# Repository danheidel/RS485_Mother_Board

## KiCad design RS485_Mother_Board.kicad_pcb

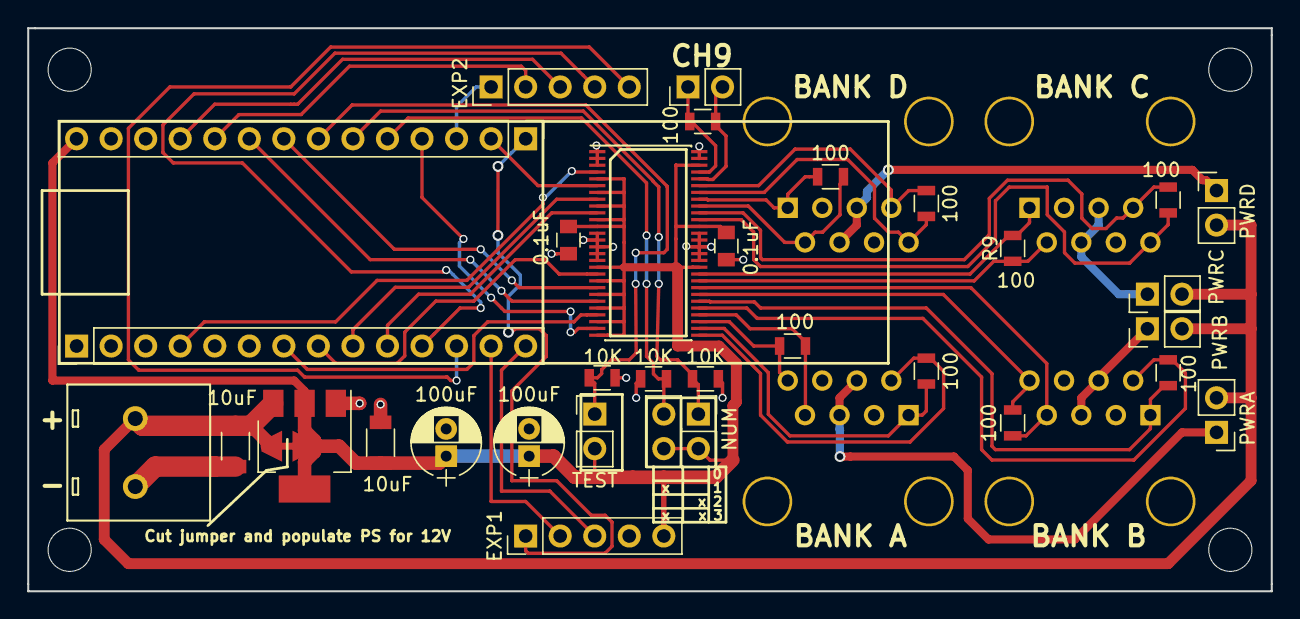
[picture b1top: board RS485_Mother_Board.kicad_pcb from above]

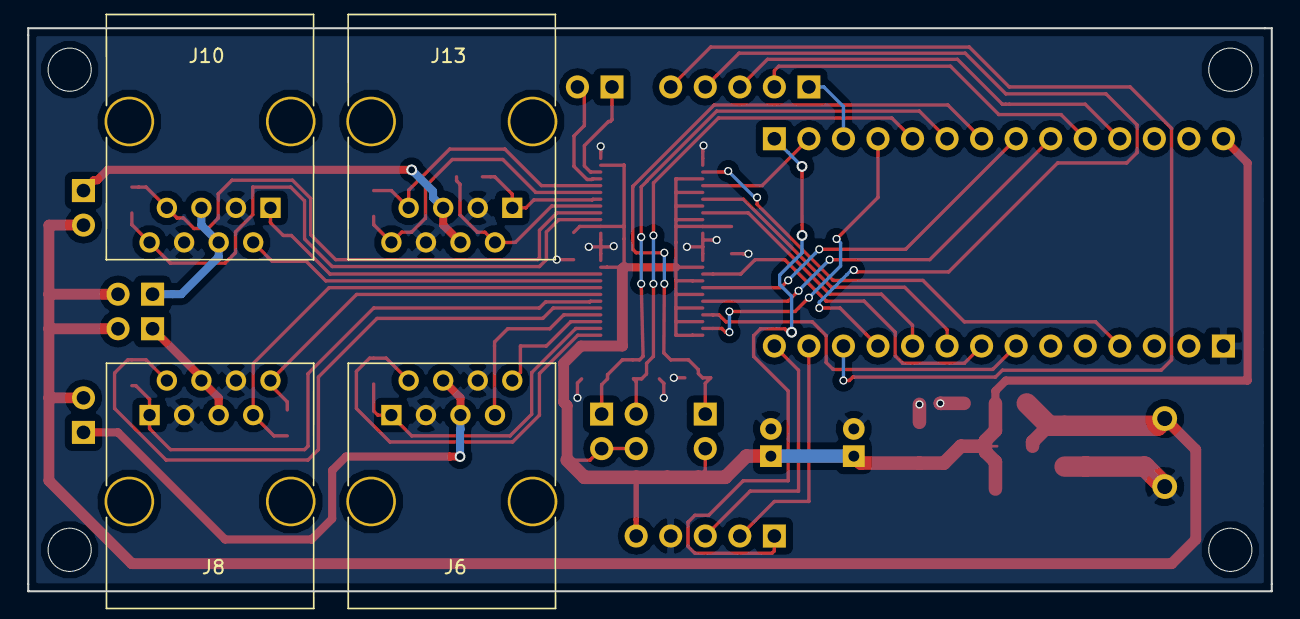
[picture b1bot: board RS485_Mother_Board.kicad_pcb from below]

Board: 2 copper layers, 91.4 x 41.4 mm, 37 parts (4 on the bottom side), 45 nets.

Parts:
C1, C2: 10uF; C_1206
C3, C4: 100uF; CP_Radial_D5.0mm_P2.00mm
C5, C6: 0.1uF; C_0805
J1: Screw_Terminal_1x02; Terminal_Block_Phoenix_SPTAF_Quick_Release_2-Pos_5mm
J2, J5: CONN_01X14; Pin_Header_Straight_1x14_Pitch2.54mm
J3: TEST; Pin_Header_Straight_1x02_Pitch2.54mm
J4: NUM; Pin_Header_Straight_2x02_Pitch2.54mm
J6: BANKA; RJ45_8
J7: PWRA; Pin_Header_Straight_1x02_Pitch2.54mm
J8: BANKB; RJ45_8
J9: PWRB; Pin_Header_Straight_1x02_Pitch2.54mm
J10: BANKC; RJ45_8
J11: CH9; Pin_Header_Straight_1x02_Pitch2.54mm
J12: PWRC; Pin_Header_Straight_1x02_Pitch2.54mm
J13: BANKD; RJ45_8
J14: PWRD; Pin_Header_Straight_1x02_Pitch2.54mm
J15: EXP2; Pin_Header_Straight_1x05_Pitch2.54mm
J16: EXP1; Pin_Header_Straight_1x05_Pitch2.54mm
JP1: Jumper
R1, R2, R3: 10K; R_0805
R4, R5, R6, R7, R8, R9, R10, R11, R12: 100; R_0805
U2: AP111733; SOT-223
U3: SN65HVD09; TSSOP-56_6.1x14mm_Pitch0.5mm(mod)

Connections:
/5V: C2.1, C3.1, C4.1, C5.2, C6.1, J3.2, J4.2, J4.4, J5.14, J16.5, JP1.2, U2.2, U2.4, U3.5, U3.7, U3.9, U3.11, U3.12, U3.18, U3.20, U3.22, U3.24, U3.26, U3.28, U3.39, U3.45, U3.54
/A1: J6.1, R4.2, U3.30
/A2: J6.7, R5.2, U3.32
/A3: J8.1, R6.2, U3.34
/A4: J8.7, R7.2, U3.36
/A5: J10.1, R9.2, U3.38
/A6: J10.7, R10.2, U3.47
/A7: J13.1, R11.2, U3.49
/A8: J13.7, R12.2, U3.51
/A9: J11.1, R8.2, U3.53
/B1: J6.2, R4.1, U3.29
/B2: J6.8, R5.1, U3.31
/B3: J8.2, R6.1, U3.33
/B4: J8.8, R7.1, U3.35
/B5: J10.2, R9.1, U3.37
/B6: J10.8, R10.1, U3.46
/B7: J13.2, R11.1, U3.48
/B8: J13.8, R12.1, U3.50
/B9: J11.2, R8.1, U3.52
/CH1: J2.4, U3.4
/CH2: J5.2, U3.6
/CH3: J2.9, U3.8
/CH4: J2.10, U3.10
/CH5: J2.8, U3.19
/CH6: J5.8, U3.21
/CH7: J5.9, U3.23
/CH8: J2.7, U3.25
/CH9: J5.4, U3.27
/CH10: J5.3, J15.1
/CH11: J5.10, J15.2
/CH12: J5.11, J15.3
/CH13: J2.11, J15.4
/CH14: J2.12, J15.5
/CH15: J5.1, J16.1
/CH16: J2.13, J16.2
/CH17: J2.14, J16.3
/NUM1: J4.1, J5.6, R2.2
/NUM2: J4.3, J5.5, R3.2
/TEST: J3.1, J5.7, R1.1
/VCC: C1.1, J1.1, J7.2, J9.2, J12.2, J14.2, JP1.1, U2.3
GND: C1.2, C2.2, C3.2, C4.2, C5.1, C6.2, J1.2, J2.1, J6.3, J6.6, J8.3, J8.6, J10.3, J10.6, J13.3, J13.6, J16.4, R1.2, R2.1, R3.1, U2.1, U3.1, U3.2, U3.3, U3.13, U3.14, U3.15, U3.16, U3.17, U3.40, U3.41, U3.42, U3.43, U3.44, U3.55, U3.56
unnamed: J6.4, J6.5, J7.1
unnamed: J8.4, J8.5, J9.1
unnamed: J10.4, J10.5, J12.1
unnamed: J13.4, J13.5, J14.1
